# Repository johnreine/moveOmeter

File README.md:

# moveOmeter

### Privacy-Preserving IoT Monitoring for Elderly Care

> Help your loved ones live independently longer with non-invasive, radar-based health monitoring.

---

## 🎯 The Problem

Families want to care for aging loved ones while respecting their independence and privacy. Traditional monitoring requires cameras (invasive) or wearables (forgotten/rejected).

## 💡 Our Solution

**moveOmeter** uses mmWave radar technology to monitor health and activity patterns without cameras or wearables. The system tracks:

- 🚶 **Activity & Movement** - Daily patterns and mobility changes
- 😴 **Sleep Quality** - Duration, disturbances, and sleep score
- ❤️ **Vital Signs** - Heart rate and respiration (contactless)
- 🚨 **Fall Detection** - Instant alerts for falls or emergencies
- 🏠 **Presence Detection** - Know when they're home or away

**No cameras. No wearables. No user interaction required.**

---

## ✨ Key Features

### Privacy-First Design
- ✅ Radar technology (sees motion, not images)
- ✅ No video, no photos, no recording
- ✅ HIPAA-compliant architecture ready

### Real-Time Monitoring
- ✅ Live web dashboard with charts
- ✅ Mobile-responsive interface
- ✅ Instant WebSocket updates
- ✅ Historical trend analysis

### Smart & Adaptive
- ✅ Learns individual patterns
- ✅ Detects anomalies automatically
- ✅ Over-the-air firmware updates
- ✅ Remote configuration

### Secure & Scalable
- ✅ Role-based access control (admin/employee/caretaker/resident)
- ✅ End-to-end encryption
- ✅ Audit logging
- ✅ Designed to scale to millions of users

---

## 📸 Screenshots

### Real-Time Dashboard
> 🚧 *Screenshot coming soon - see [deployment guide](./deployment/QUICKSTART.md) to run locally*

**Features visible in dashboard:**
- Live timeline charts (1-hour, 12-hour, 24-hour views)
- Activity metrics (movement, presence, sleep quality)
- Device status (online/offline)
- Manual annotations
- Alert notifications

### Admin Panel
> 🚧 *Screenshot coming soon*

**Manage users and devices:**
- User management (create, edit, roles)
- Device assignment
- Access control
- Audit logs

---

## 🚀 Quick Start

### Prerequisites
- ESP32-C6 Feather development board
- DFRobot SEN0623 mmWave sensor
- Supabase account (free tier works)
- Arduino IDE 2.x

### 5-Minute Setup

1. **Clone the repository**
   ```bash
   git clone https://github.com/johnreine/moveOmeter.git
   cd moveOmeter
   ```

2. **Set up database**
   - Create Supabase project at https://supabase.com
   - Run migrations: `database/run_all_migrations.sql`

3. **Configure firmware**
   ```bash
   # Edit pictureFrame/software/mmWave_Supabase_collector/config.h
   # Add your WiFi credentials and Supabase URL/key
   ```

4. **Upload to ESP32-C6**
   - Open Arduino IDE
   - Select board: ESP32C6 Dev Module
   - Upload sketch

5. **Start dashboard**
   ```bash
   cd web/dashboard
   python3 -m http.server 8000
   open http://localhost:8000
   ```

**Full setup guide:** [deployment/QUICKSTART.md](./deployment/QUICKSTART.md)

---

## 🏗️ Architecture

```
┌──────────────────────────────────────────────────────┐
│  ESP32-C6 + mmWave Sensor (DFRobot SEN0623)         │
│  • Collects 40+ health metrics every 20 seconds     │
│  • WiFi upload to cloud                             │
│  • OTA firmware updates                             │
└─────────────────┬────────────────────────────────────┘
                  │ HTTPS Upload
                  ▼
┌──────────────────────────────────────────────────────┐
│  Supabase Backend (PostgreSQL + Auth + Realtime)    │
│  • Time-series sensor data storage                  │
│  • Role-based access control (RLS)                  │
│  • Real-time WebSocket subscriptions                │
│  • OTA firmware distribution                        │
└─────────────────┬────────────────────────────────────┘
                  │ WebSocket + REST API
                  ▼
┌──────────────────────────────────────────────────────┐
│  Web Dashboard (Vanilla JS + Chart.js)              │
│  • Live charts and metrics                          │
│  • User authentication                              │
│  • Admin panel                                      │
│  • Mobile responsive                                │
└──────────────────────────────────────────────────────┘
```

---

## 🛠️ Tech Stack

### Hardware

### Backend

### Frontend

### Firmware

### Deployment

---

## 📚 Documentation

| Document | Description |
|----------|-------------|
| **[Project Status](./PROJECT_STATUS.md)** | Complete overview of features and progress |
| **[Development Roadmap](./ROADMAP.md)** | 6-12 month development plan |
| **[AI Agent Guide](./AI_AGENT_GUIDE.md)** | For AI coding assistants (Claude, GPT, etc.) |
| **[Quick Start](./deployment/QUICKSTART.md)** | Get running in 5 minutes |
| **[Full Deployment Guide](./deployment/README.md)** | Production deployment instructions |
| **[Authentication Setup](./web/dashboard/AUTH_SETUP.md)** | User management and security |
| **[Firmware README](./pictureFrame/software/mmWave_Supabase_collector/README.md)** | ESP32-C6 firmware details |
| **[OTA Testing Guide](./database/OTA_QUICK_TEST.md)** | Test firmware updates |

---

## 🗺️ Roadmap

### ✅ Current (v1.0) - Complete
- ESP32-C6 firmware with dual collection modes
- Real-time web dashboard with charts
- Authentication system (4 user roles)
- Admin panel for user/device management
- OTA firmware update infrastructure
- Timeline annotations
- Data aggregation for performance

### 🚧 Next Month (v1.1)
- [ ] Multi-device support in dashboard
- [ ] Progressive Web App (PWA)
- [ ] Email notifications
- [ ] Activity summary reports
- [ ] Mobile-responsive design improvements

### 🔮 Next Quarter (v1.5)
- [ ] React Native mobile app (iOS + Android)
- [ ] Predictive health alerts (ML-based)
- [ ] Medication reminder integration
- [ ] Voice integration (Alexa/Google Home)
- [ ] Family sharing features

### 🎯 Long-Term Vision
- AI-powered gait analysis and fall risk prediction
- Behavior pattern recognition
- White-label solution for senior living facilities
- Integration ecosystem (Apple Health, etc.)

**Full roadmap:** [ROADMAP.md](./ROADMAP.md)

---

## 🤝 Contributing

We welcome contributions! This project is currently in active development.

### How to Contribute

1. **Read the docs**
   - [Project Status](./PROJECT_STATUS.md) - Current state
   - [Roadmap](./ROADMAP.md) - Planned features
   - [AI Agent Guide](./AI_AGENT_GUIDE.md) - Technical details

2. **Find an issue**
   - Check [Issues](https://github.com/johnreine/moveOmeter/issues) for open tasks
   - Look for `good first issue` or `help wanted` labels

3. **Fork and create a branch**
   ```bash
   git checkout -b feature/your-feature-name
   ```

4. **Make your changes**
   - Follow existing code style
   - Add tests if applicable
   - Update documentation

5. **Submit a pull request**
   - Clear description of changes
   - Reference related issues
   - Screenshots for UI changes

### Development Setup

```bash
# Clone repository
git clone https://github.com/johnreine/moveOmeter.git
cd moveOmeter

# Install Arduino libraries
# - ESPSupabase (by jhagas)
# - DFRobot_HumanDetection (by DFRobot)

# Set up Supabase
# 1. Create account at https://supabase.com
# 2. Run database/run_all_migrations.sql

# Start local dashboard
cd web/dashboard
python3 -m http.server 8000
```

### Code Style

- **JavaScript:** ES6+, async/await, template literals
- **C++:** Arduino style, comments for complex logic
- **SQL:** Uppercase keywords, clear comments
- **Documentation:** Markdown with clear headings

---

## 🌟 Use Cases

### For Families
- Monitor aging parents remotely
- Peace of mind while at work
- Early detection of health changes
- Respect privacy (no cameras)

### For Caregivers
- Track multiple clients
- Shift handoff notes
- Medication reminders
- Fall alerts

### For Senior Living Facilities
- Monitor all residents
- Staff coordination
- Compliance reporting
- Emergency response

### For Healthcare Providers
- Remote patient monitoring
- Post-discharge tracking
- Chronic condition management
- Reduce hospital readmissions

---

## 📊 Project Stats

- **40 files** of comprehensive documentation
- **16,000+ lines** of code and docs
- **40+ sensor metrics** collected
- **4 user roles** with granular permissions
- **3 timeline views** (1h, 12h, 24h)
- **97% bandwidth reduction** with smart keep-alive
- **OTA updates** for remote firmware deployment

---

## 🔐 Security & Privacy

### Privacy Protections
- ✅ No cameras or video recording
- ✅ Radar technology (motion only, not images)
- ✅ Data encrypted in transit (HTTPS)
- ✅ Data encrypted at rest (Supabase)
- ✅ Row Level Security (RLS) for data isolation

### Compliance Ready
- 🔜 HIPAA compliance architecture
- 🔜 GDPR data handling
- 🔜 SOC 2 Type II準備中

### Security Features
- Multi-factor authentication (MFA) support
- Passkey/WebAuthn ready
- Audit logging for all actions
- Role-based access control
- Automatic session management

---

## 🛡️ Testing

### Current Test Coverage
- ✅ End-to-end firmware testing
- ✅ Real-time data pipeline
- ✅ Authentication flows
- ✅ Role-based access control
- 🚧 Cross-browser compatibility
- 🚧 Scale testing (100-1000 devices)

### Tested Environments
- **Firmware:** ESP32-C6 Feather
- **Browsers:** Chrome, Firefox, Safari (desktop)
- **Database:** Supabase (PostgreSQL 15)
- **Deployment:** Ubuntu 22.04 + Nginx

---

## 💰 Cost to Run

### Development (Current)
- **Supabase:** Free tier (good for 10 devices)
- **Digital Ocean:** $10-20/month
- **Total:** ~$10-20/month

### Small Deployment (100 devices)
- **Supabase:** $25/month (Pro tier)
- **Digital Ocean:** $20/month
- **Total:** ~$45/month

### Medium Scale (1,000 devices)
- **Supabase:** $599/month (Team tier)
- **Digital Ocean/AWS:** $100-200/month
- **Total:** ~$700-800/month

**Note:** Costs scale linearly. See [ROADMAP.md](./ROADMAP.md) for scaling details.

---

## 📄 License

**Proprietary** - All rights reserved.

This project is currently not open source. Contact for licensing inquiries.

---

## 📞 Contact & Support

### Questions or Issues?
1. Check [Project Status](./PROJECT_STATUS.md) and [Roadmap](./ROADMAP.md)
2. Review [documentation](./deployment/README.md)
3. Open an [Issue](https://github.com/johnreine/moveOmeter/issues)

### Business Inquiries
- **Email:** contact@moveometer.com (TBD)
- **Website:** https://moveometer.com (TBD)

### For Contributors
- Join discussions in [Issues](https://github.com/johnreine/moveOmeter/issues)
- Submit [Pull Requests](https://github.com/johnreine/moveOmeter/pulls)
- See [AI Agent Guide](./AI_AGENT_GUIDE.md) for technical details

---

## 🙏 Acknowledgments

### Hardware
- **Adafruit** - ESP32-C6 Feather development board
- **DFRobot** - SEN0623 mmWave sensor

### Software & Services
- **Supabase** - Backend-as-a-Service platform
- **Chart.js** - Beautiful data visualization
- **Arduino** - ESP32 development framework

### Inspiration
Built with care for families supporting elderly loved ones. Inspired by the need for privacy-preserving health monitoring that maintains dignity and independence.

---

## ⭐ Star History

If you find this project useful, consider giving it a star! ⭐

---

## 📈 Project Activity

---

<div align="center">

**Made with ❤️ for better elderly care**

[Documentation](./PROJECT_STATUS.md) • [Roadmap](./ROADMAP.md) • [Contributing](#contributing) • [License](#license)

</div>

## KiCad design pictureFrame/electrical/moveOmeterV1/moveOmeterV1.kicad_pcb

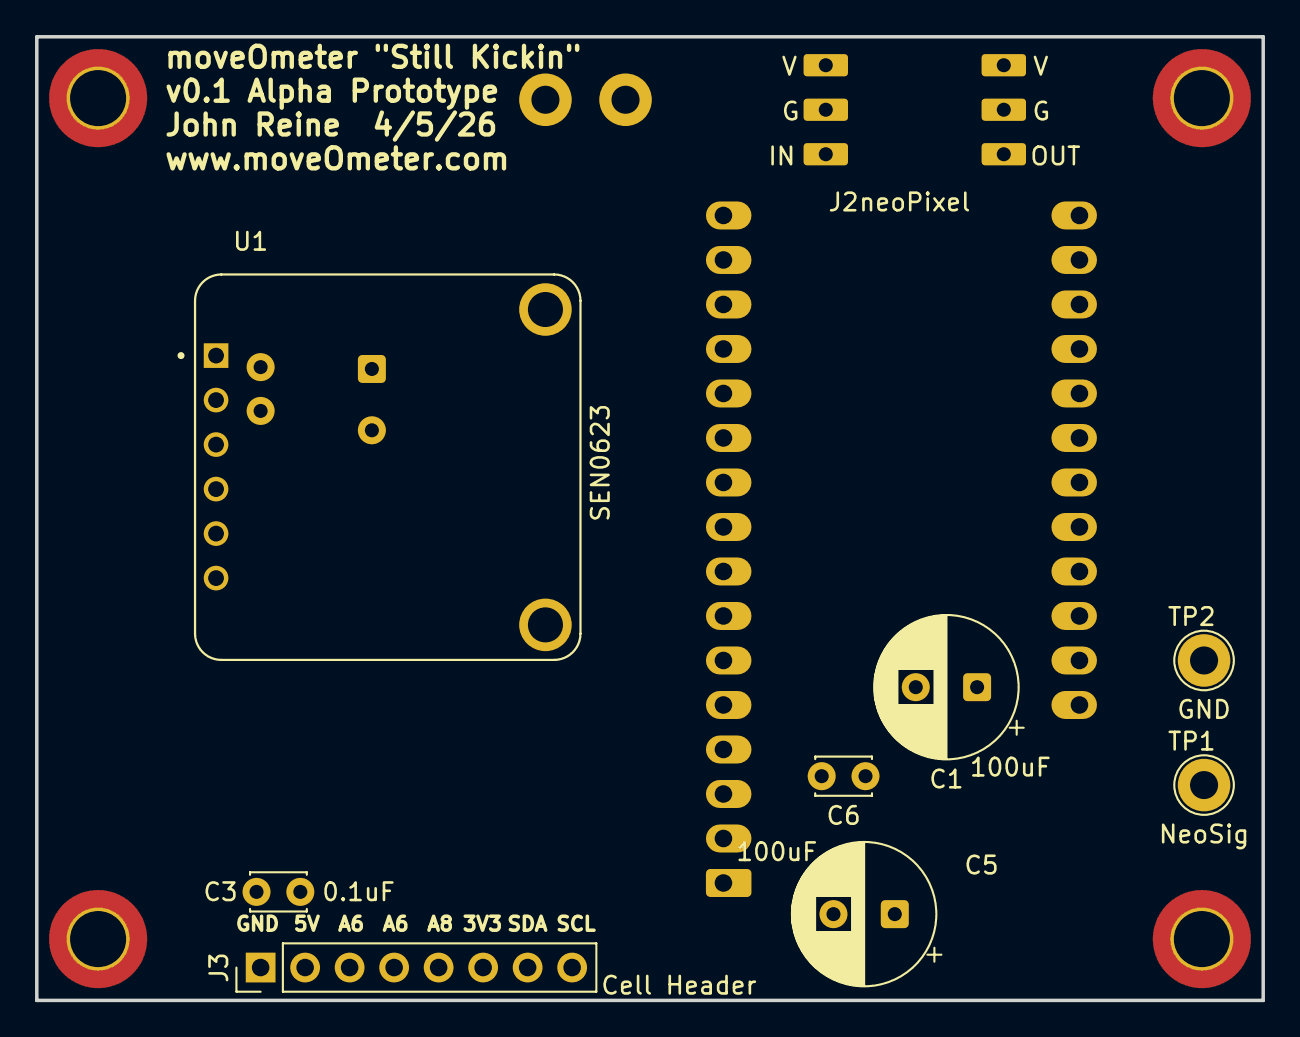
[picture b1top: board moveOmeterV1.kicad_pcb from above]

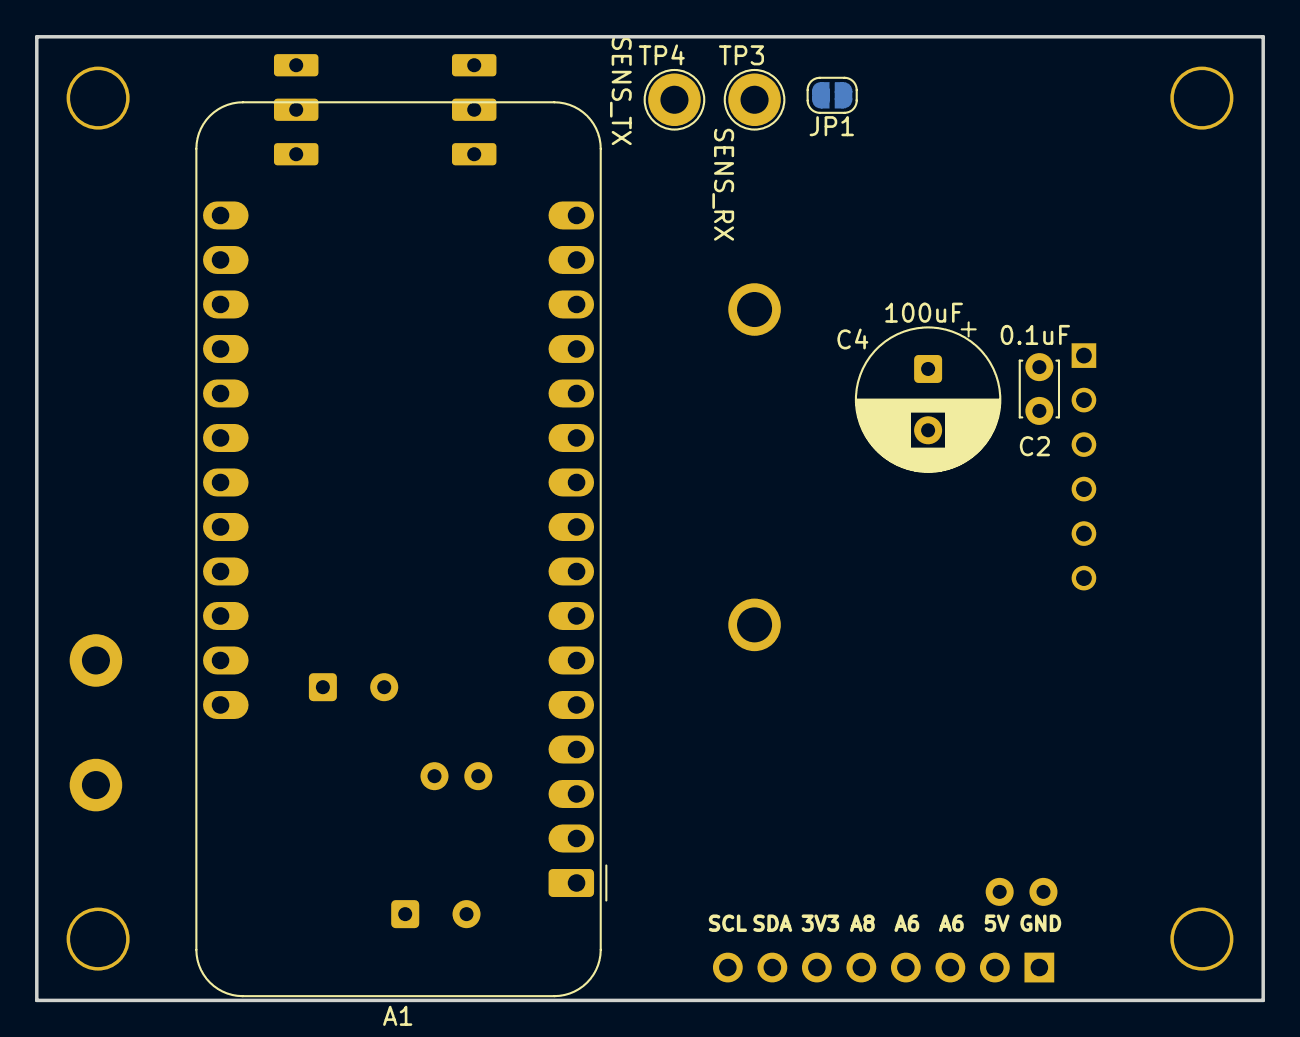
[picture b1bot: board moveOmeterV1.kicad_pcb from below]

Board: 2 copper layers, 70.0 x 55.0 mm, 15 parts (6 on the bottom side), 13 nets, no tracks yet.

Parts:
A1: Adafruit_Feather_ESP32-C6; Adafruit_Feather
C1, C4, C5: 100uF; CP_Radial_D8.0mm_P3.50mm
C2, C3, C6: 0.1uF; C_Disc_D3.0mm_W2.0mm_P2.50mm
J2: neoPixel; neoPixel6pin
J3: Cell Header; PinHeader_1x08_P2.54mm_Vertical
JP1: SolderJumper_2_Open; SolderJumper-2_P1.3mm_Open_RoundedPad1.0x1.5mm
TP1: NeoSig; TestPoint_Loop_D2.60mm_Drill1.6mm_Beaded
TP2: GND; TestPoint_Loop_D2.60mm_Drill1.6mm_Beaded
TP3: SENS_RX; TestPoint_Loop_D2.60mm_Drill1.6mm_Beaded
TP4: SENS_TX; TestPoint_Loop_D2.60mm_Drill1.6mm_Beaded
U1: SEN0623; MODULE_SEN0623

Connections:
+3V3 500mA: A1.2 (3V3), J2.1, J3.6
/5V_USB: A1.26 (USB), C1.1, C2.1, C3.1, C4.1, C5.1, C6.1, J3.2, U1.1 (VIN)
/A3: A1.8 (I39/A3), J2.3, TP1.1
/A6: A1.19 (A6/IO14), J3.4
/A7: A1.20 (A7/IO32), J3.3
/A8: A1.21 (A8/IO15), J3.5
/A9: A1.22 (A9/IO33), U1.6 (IO2)
/SCL: A1.6 (DAC1/A1), J3.8
/SDA: A1.7 (I34/A2), J3.7
/SENS_RX: A1.14 (RX/IO16), TP3.1, U1.4 (TX)
/SENS_TX: A1.15 (TX/IO17), TP4.1, U1.3 (RX)
GND: A1.4 (GND), C1.2, C2.2, C3.2, C4.2, C5.2, C6.2, J2.2, J3.1, JP1.1 (A), TP2.1, U1.2 (GND)
unnamed: A1.5 (DAC2/A0), U1.5 (IO1)
